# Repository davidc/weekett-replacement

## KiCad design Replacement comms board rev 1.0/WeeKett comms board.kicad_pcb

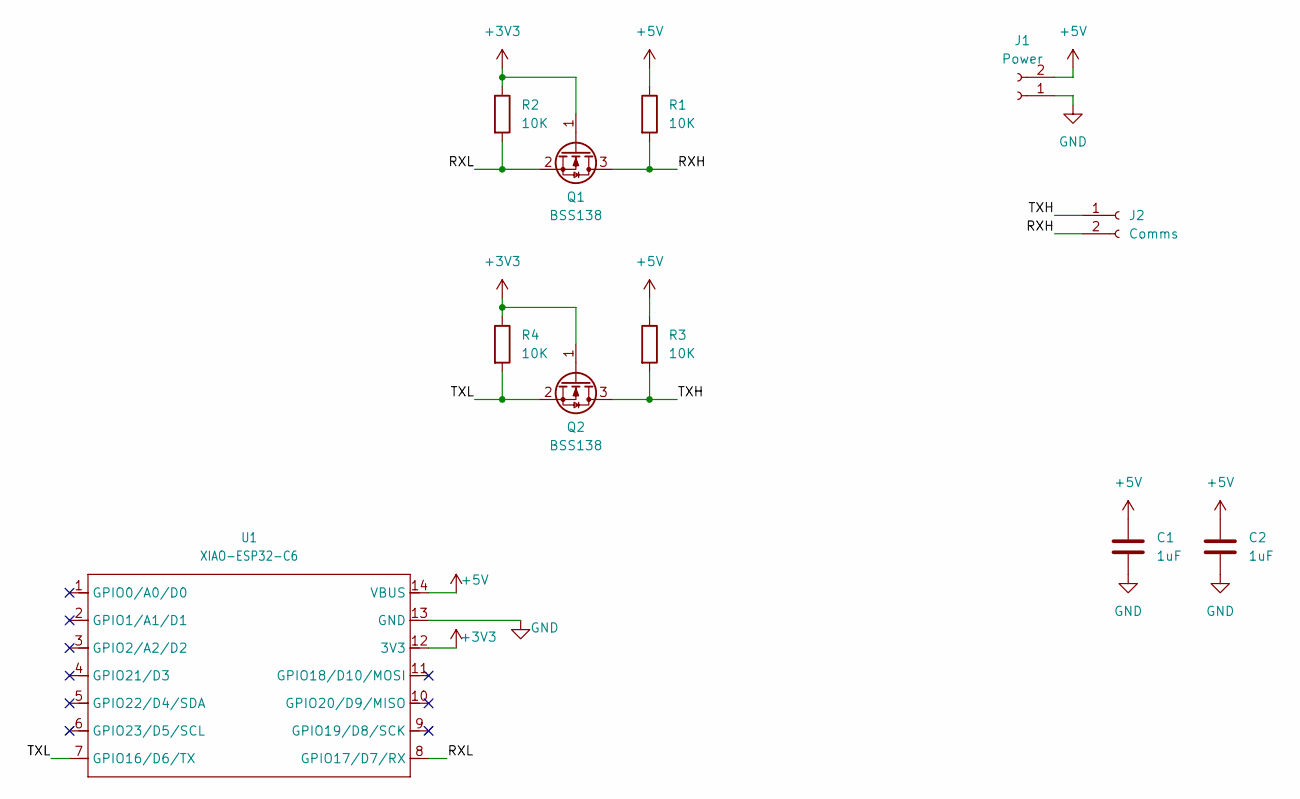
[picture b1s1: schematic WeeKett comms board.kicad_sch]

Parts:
C1, C2: 1uF; C_0805_2012Metric
J1: Power; JST_XH_S2B-XH-A_1x02_P2.50mm_Horizontal
J2: Comms; JST_XH_S2B-XH-A_1x02_P2.50mm_Horizontal
Q1, Q2: BSS138; SOT-23
R1, R2, R3, R4: 10K; R_0805_2012Metric
U1: XIAO-ESP32-C6; XIAO-ESP32C6-DIP

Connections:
+3V3: Q1.1 (G), Q2.1 (G), R2.1, R4.1, U1.12 (3V3)
+5V: C1.1, C2.1, J1.2, R1.1, R3.1, U1.14 (VBUS)
/RXH: J2.2, Q1.3 (D), R1.2
/RXL: Q1.2 (S), R2.2, U1.8 (GPIO17/D7/RX)
/TXH: J2.1, Q2.3 (D), R3.2
/TXL: Q2.2 (S), R4.2, U1.7 (GPIO16/D6/TX)
GND: C1.2, C2.2, J1.1, U1.13 (GND)

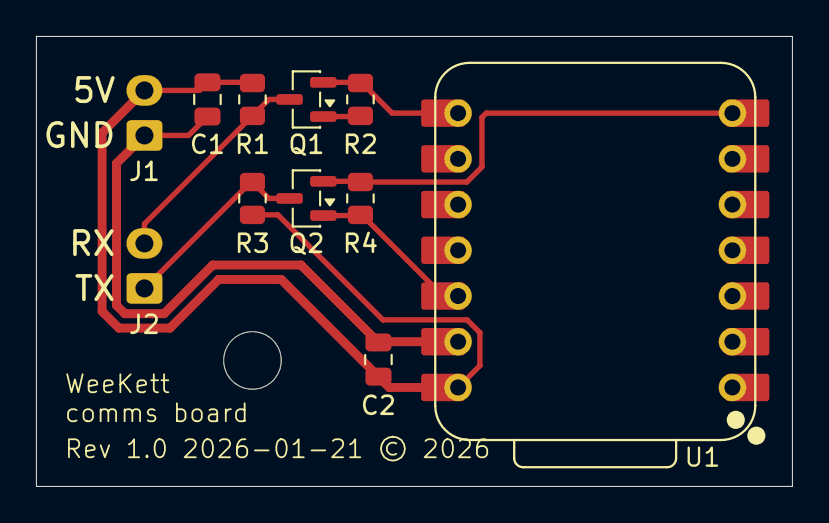
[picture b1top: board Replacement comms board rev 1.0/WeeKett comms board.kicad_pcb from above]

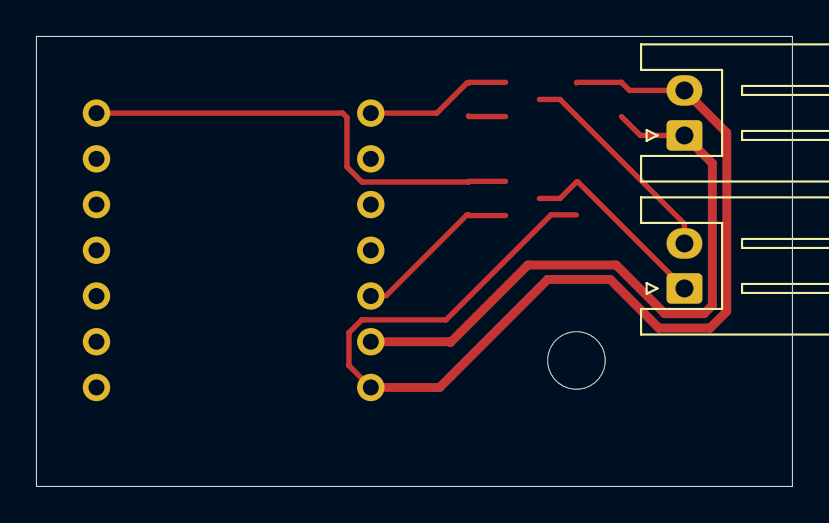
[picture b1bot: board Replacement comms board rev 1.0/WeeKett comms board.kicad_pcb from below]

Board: 2 copper layers, 42.0 x 25.0 mm, 11 parts (2 on the bottom side), 7 nets.

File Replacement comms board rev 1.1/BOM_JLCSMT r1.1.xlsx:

Comment | Designator | Footprint | JLCPCB Part #（optional）
1uF | C1 | 0805 | C28323
100nF | C2 | 0805 | C28233
BSS138 | Q1,Q2 | SOT-23 | C7420339
10k | R1,R2,R3,R4 | 0805 | C17414

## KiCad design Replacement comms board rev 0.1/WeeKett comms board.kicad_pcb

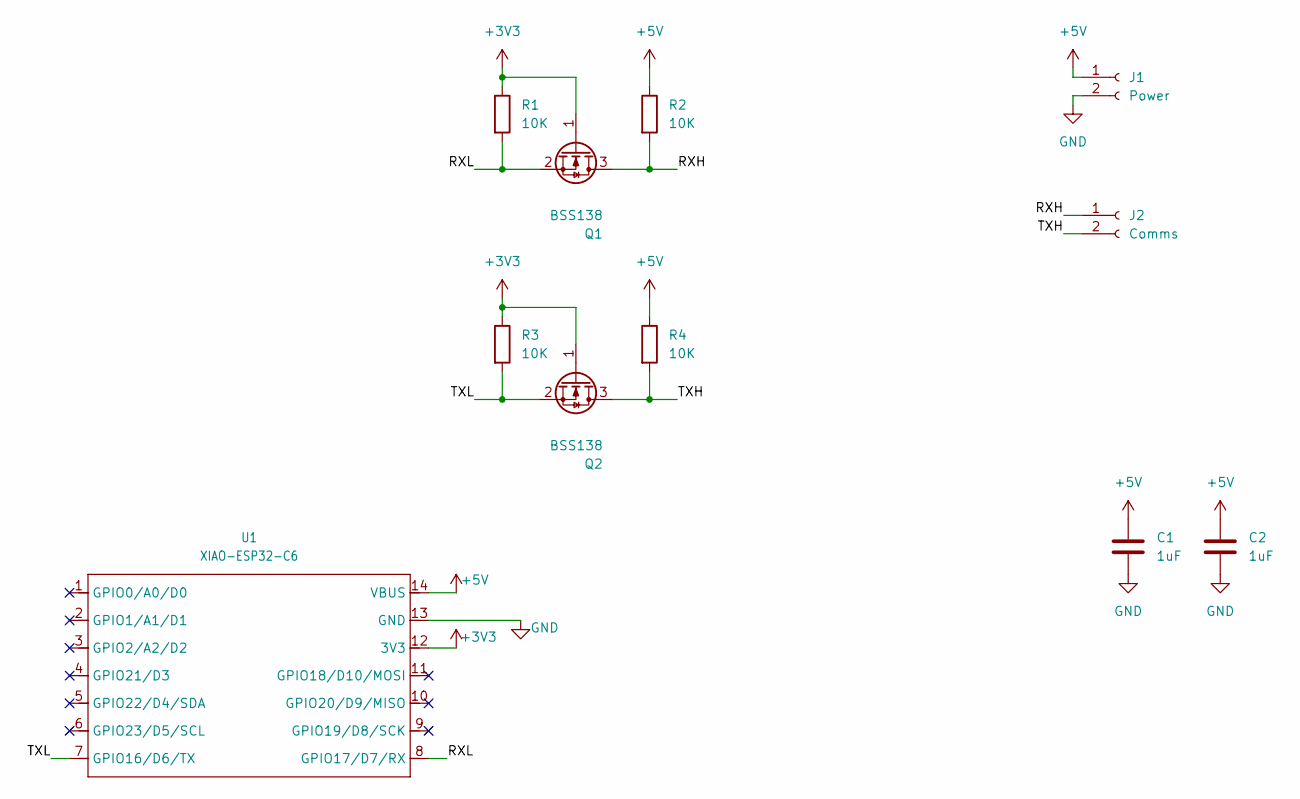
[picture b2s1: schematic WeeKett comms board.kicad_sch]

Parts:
C1, C2: 1uF; C_0603_1608Metric
J1: Power; PinHeader_1x02_P2.54mm_Vertical
J2: Comms; PinHeader_1x02_P2.54mm_Vertical
Q1, Q2: BSS138; SOT-23
R1, R2, R3, R4: 10K; R_0603_1608Metric
U1: XIAO-ESP32-C6; XIAO-ESP32C6-DIP

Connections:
+3V3: Q1.1 (G), Q2.1 (G), R1.1, R3.1, U1.12 (3V3)
+5V: C1.1, C2.1, J1.1, R2.1, R4.1, U1.14 (VBUS)
/RXH: J2.1, Q1.3 (D), R2.2
/RXL: Q1.2 (S), R1.2, U1.8 (GPIO17/D7/RX)
/TXH: J2.2, Q2.3 (D), R4.2
/TXL: Q2.2 (S), R3.2, U1.7 (GPIO16/D6/TX)
GND: C1.2, C2.2, J1.2, U1.13 (GND)

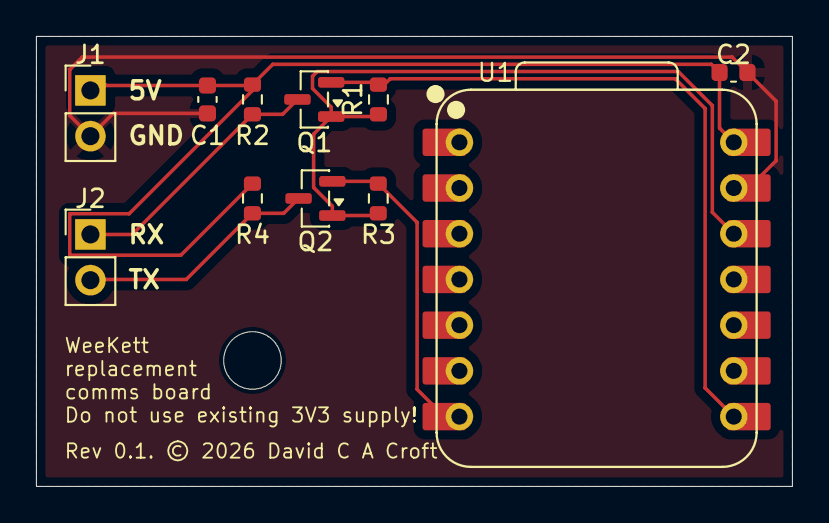
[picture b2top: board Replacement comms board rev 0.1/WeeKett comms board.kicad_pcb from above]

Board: 2 copper layers, 42.0 x 25.0 mm, 11 parts (0 on the bottom side), 7 nets.

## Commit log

2026-03-06 Initial schematic and PCB import
2026-03-06 initial esphome config
2026-03-08 initial attempts to use an esphome water_heater don't publish current temperature if kettle is off-hook

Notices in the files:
Replacement comms board rev 0.1/WeeKett comms board.kicad_pcb:
Rev 0.1. © 2026 David C A Croft
Replacement comms board rev 1.0/WeeKett comms board.kicad_pcb:
Rev 1.0 2026-01-21 © 2026
